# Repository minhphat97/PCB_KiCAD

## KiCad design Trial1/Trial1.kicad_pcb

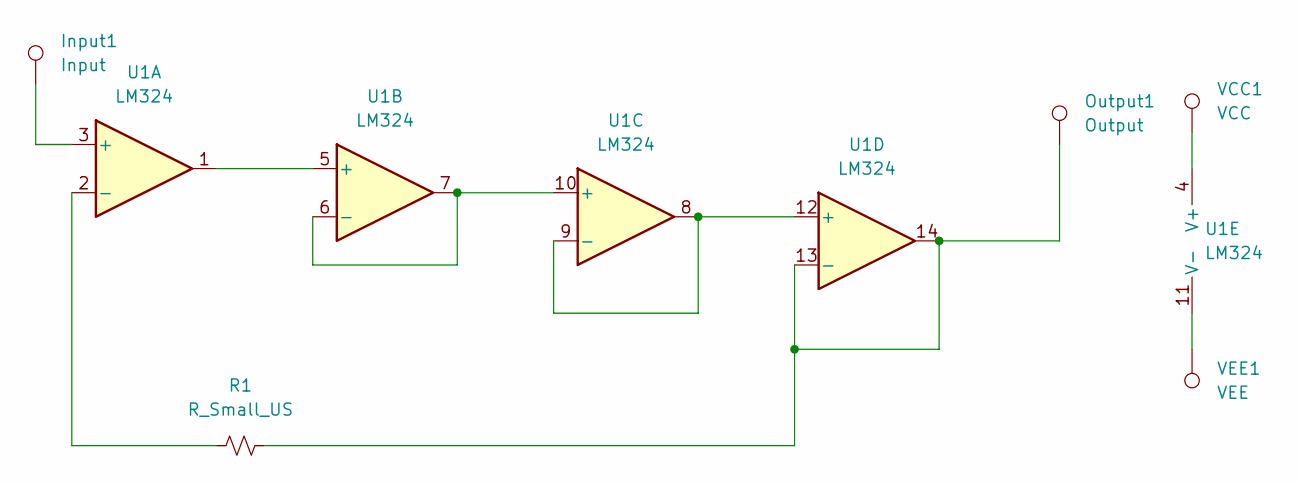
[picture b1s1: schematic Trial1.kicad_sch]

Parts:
Input1: Input; TestPoint_Keystone_5000-5004_Miniature
Output1: Output; TestPoint_Keystone_5000-5004_Miniature
R1: R_Small_US; R_Axial_DIN0207_L6.3mm_D2.5mm_P10.16mm_Horizontal
U1: LM324; DIP-14_W8.89mm_SMDSocket_LongPads
VCC1: VCC; TestPoint_Keystone_5000-5004_Miniature
VEE1: VEE; TestPoint_Keystone_5000-5004_Miniature

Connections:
unnamed: Input1.1, U1.3 (+)
unnamed: R1.1, U1.2 (-)
unnamed: U1.1, U1.5 (+)
unnamed: U1.6 (-), U1.7, U1.10 (+)
unnamed: U1.8, U1.9 (-), U1.12 (+)
unnamed: Output1.1, R1.2, U1.13 (-), U1.14
unnamed: U1.4 (V+), VCC1.1
unnamed: U1.11 (V-), VEE1.1

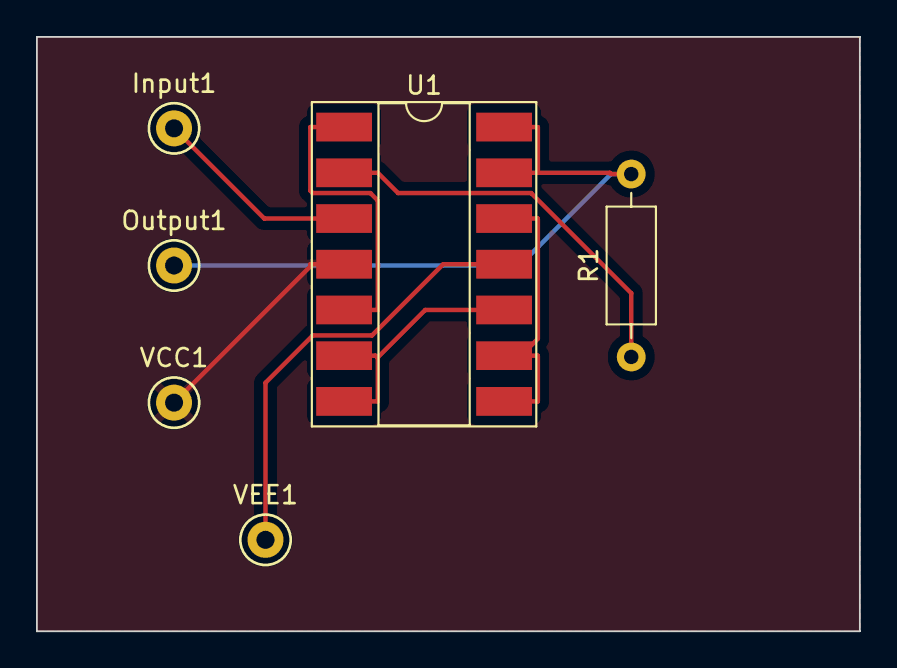
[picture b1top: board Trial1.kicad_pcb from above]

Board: 2 copper layers, 45.7 x 33.0 mm, 6 parts (0 on the bottom side), 8 nets.

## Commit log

2023-08-20 Cascade op amp 3D design
